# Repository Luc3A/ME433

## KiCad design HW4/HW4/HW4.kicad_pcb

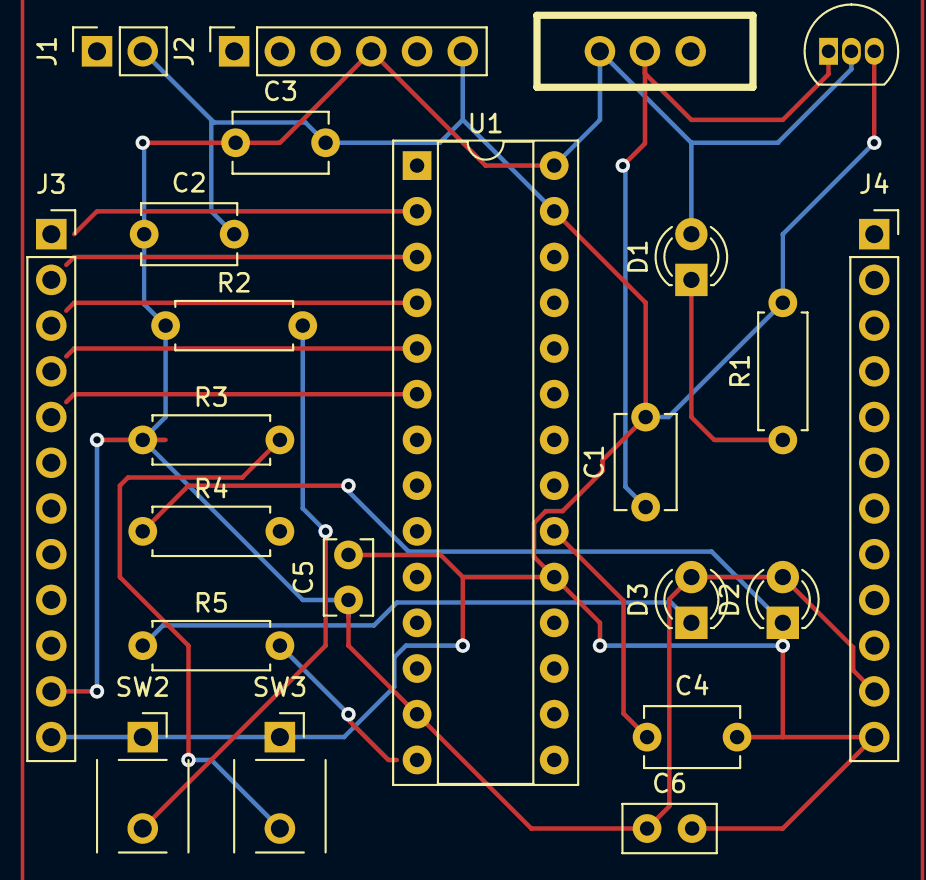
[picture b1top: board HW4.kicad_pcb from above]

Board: 2 copper layers, 23 parts (0 on the bottom side), 9 nets.

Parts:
C1, C2, C3: C; C_Disc_D5.1mm_W3.2mm_P5.00mm
C4: 1uF; C_Disc_D5.1mm_W3.2mm_P5.00mm
C5: 0.1uF; C_Rect_L4.0mm_W2.5mm_P2.50mm
C6: 0.1uF; C_Disc_D5.0mm_W2.5mm_P2.50mm
D1: RED; LED_D3.0mm
D2, D3: LED; LED_D3.0mm
J1: BATTERY; PinSocket_1x02_P2.54mm_Vertical
J2: CP2102; PinSocket_1x06_P2.54mm_Vertical
J3: LEFT; PinSocket_1x12_P2.54mm_Vertical
J4: RIGHT; PinSocket_1x12_P2.54mm_Vertical
R1, R4, R5: 330; R_Axial_DIN0207_L6.3mm_D2.5mm_P7.62mm_Horizontal
R2, R3: 10k; R_Axial_DIN0207_L6.3mm_D2.5mm_P7.62mm_Horizontal
SW1: SW_slide; slidesw2
SW2: MCLR; PB
SW3: USER; PB
U1: DIP-28_W7.62mm_Socket
U2: AP7381-33V; TO-92_Inline

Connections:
+3.3V: C2.1, C3.1, C5.1, C6.1, D1.2 (A), D2.2 (A), D3.2 (A), J2.4, J3.11, J4.11, R2.1, R3.1, SW1.1 (A), U1.13 (Vdd), U1.28 (AVdd), U2.2 (VO)
GND: C1.2, C2.2, C3.2, C4.2, C5.2, C6.2, J1.2, J2.6, J3.12, J4.12, R1.2, SW2.1, SW3.1, U1.8 (Vss), U1.19 (Vss), U1.27 (AVss), U2.3 (GND)
unnamed: D1.1 (K), R1.1
unnamed: D2.1 (K), R4.1
unnamed: D3.1 (K), R5.1
unnamed: R2.2, SW2.2
unnamed: R3.2, SW3.2
unnamed: C1.1, SW1.2 (B), U2.1 (VI)
unnamed: C4.1, U1.20 (Vcap)

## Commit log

2023-04-04 Homework 2
    Files for Homework 2
2023-04-09 Homework 3
    Final Homework 3
2023-04-18 Homework 4
2023-05-29 HW Update
2023-05-29 HW Update 2
2023-05-29 HW7 update
2023-05-31 HW8 Update
2023-06-04 HW10 Update
2023-06-05 HW11 Update
2023-06-05 HW15 Update
2023-06-05 HW 14 Update
2023-06-08 HW 16
2023-06-08 HW16
